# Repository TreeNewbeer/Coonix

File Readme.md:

# Coonix

_Coonix_ is a funny project about building a application platform in Allwinner-v3s processor or nuvoton nuc980 processor.

### The structure of _Coonix_ is shown as follow:

## How to use
* TODO

## TODO
* Hardware schematic diagram
* Linux porting

## License

* MIT License

## Contributing

If you are pleased with this project, give me _Star_ rather than coffee:)

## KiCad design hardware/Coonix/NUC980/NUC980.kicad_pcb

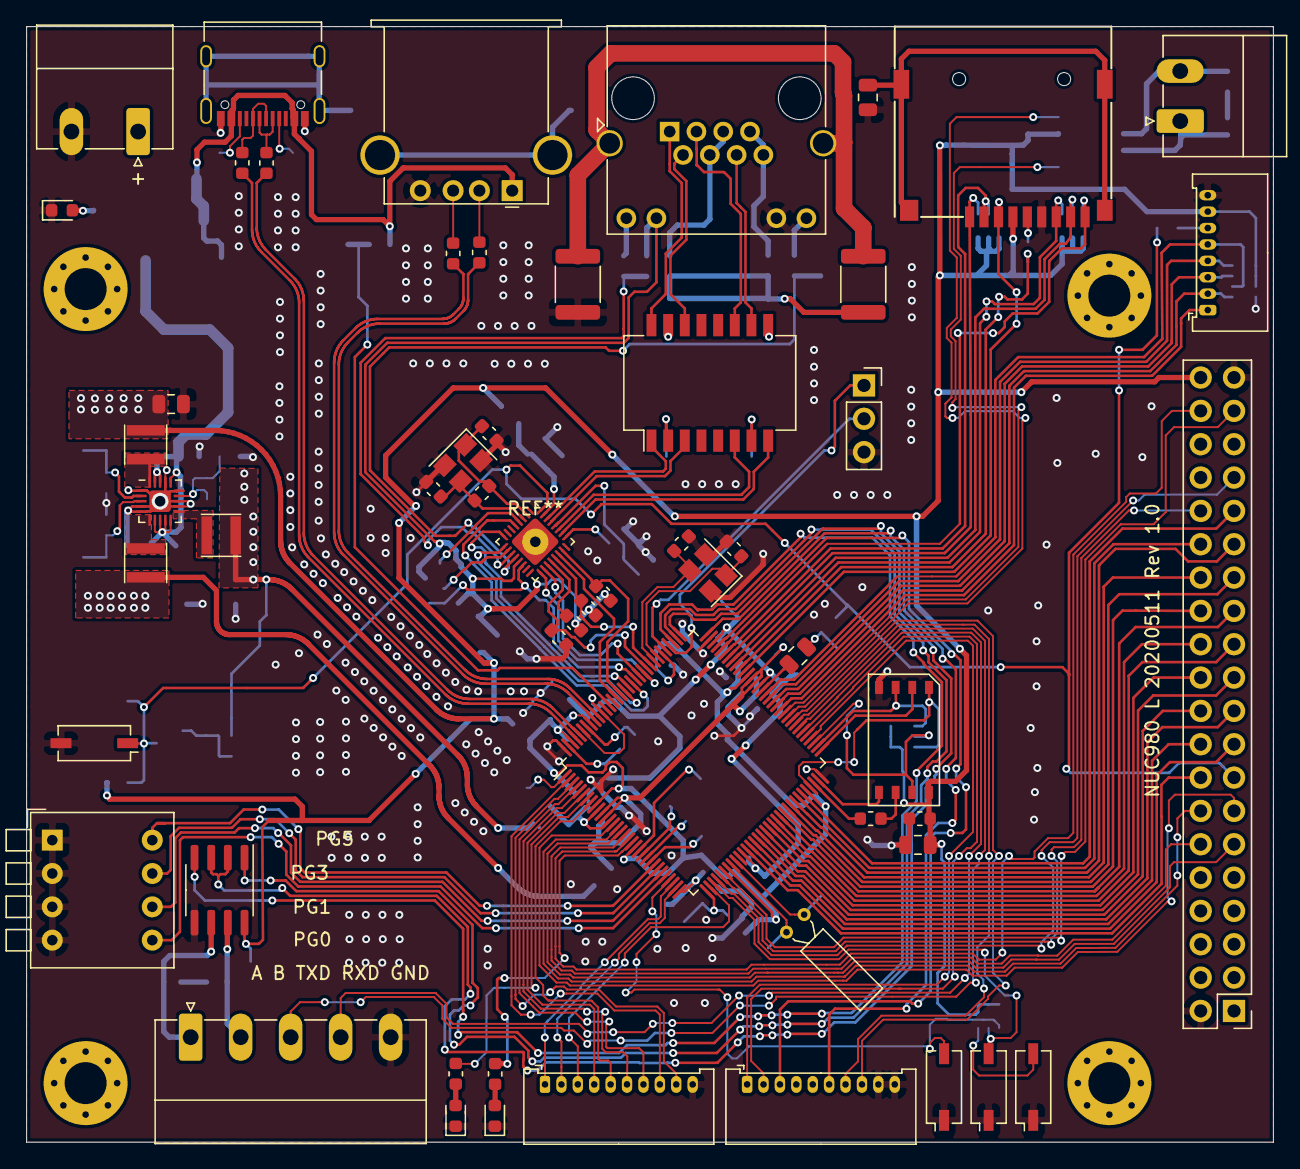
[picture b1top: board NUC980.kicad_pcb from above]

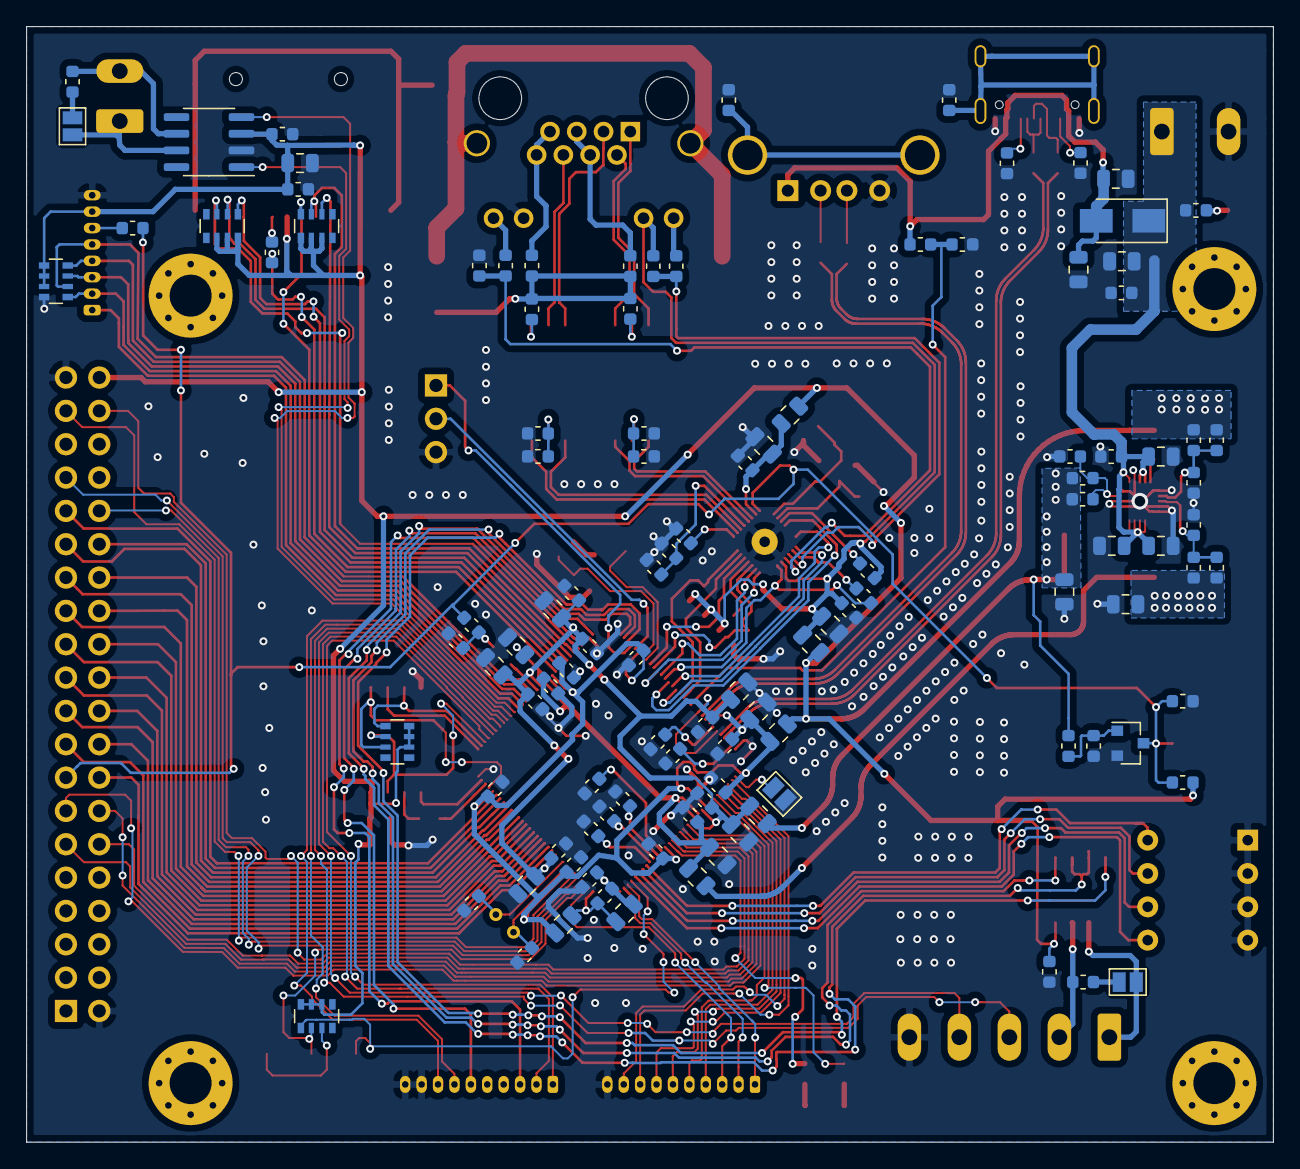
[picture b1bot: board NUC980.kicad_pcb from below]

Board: 2 copper layers, 95.0 x 85.0 mm, 171 parts (112 on the bottom side), 172 nets.

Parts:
C201, C202: 0.01uF/2KV; C_1812_4532Metric
C203, C205, C207, C303, C304: 0.01uF; C_0603_1608Metric
C204, C206, C208, C212, C213, C305, C402, C501, C711, C713, C714, C715, C716, C717, C718, C720, C722, C724, C726, C728, C729, C731, C735, C737, C1001, C1101: 0.1uF; C_0603_1608Metric
C209, C214: 30pF; C_0603_1608Metric
C210, C211, C301, C302, C306, C401, C502, C707, C708, C710, C719, C721, C723, C725, C727, C730, C736, C738, C739, C740, C741, C742: 10uF; C_0805_2012Metric
C701, C702, C704, C705: 15pF; C_0603_1608Metric
C703: 1nF; C_0603_1608Metric
C706, C709, C712: 1uF; C_0603_1608Metric
C732, C733, C734: 18pF; C_0603_1608Metric
D301, D1202: GREEN; LED_0603_1608Metric
D302: SS14; D_SMA
D1201: RED; LED_0603_1608Metric
FB201, FB202, FB501, FB701, FB702, FB703, FB704, FB705: 120R; L_0805_2012Metric
H301, H302, H303, H304: MountingHole; MountingHole_3.2mm_M3_Pad_Via
J201: 8P8C_LED_Shielded; RJ45_Amphenol_RJHSE538X
J301: USB_A; USB_A_Stewart_SS-52100-001_Horizontal
J302: USB_C_Receptacle; USB_C_Receptacle_Palconn_UTC16-G
J303: POWER; PhoenixContact_MC_1,5_2-G-5.08_1x02_P5.08mm_Horizontal
J501: Micro_SD_Card; MicroSD
J601, J901: Conn_01x10; Molex_PicoBlade_53048-1010_1x10_P1.25mm_Horizontal
J701: Debug_UART; PinSocket_1x03_P2.54mm_Vertical
J702: JTAG; Molex_PicoBlade_53048-0810_1x08_P1.25mm_Horizontal
J801: AC1583; PinHeader_2x20_P2.54mm_Vertical
J1001: Conn_01x05; PhoenixContact_MC_1,5_5-G-3.81_1x05_P3.81mm_Horizontal
J1101: Conn_01x02; PhoenixContact_MC_1,5_2-G-3.81_1x02_P3.81mm_Horizontal
JP301: USB0 Host/Device; SolderJumper-2_P1.3mm_Open_Pad1.0x1.5mm
JP1001, JP1101: JP; SolderJumper-2_P1.3mm_Open_Pad1.0x1.5mm
L701, L702, L703: 2.2uH 1.5A; L_Taiyo-Yuden_NR-30xx
Q701: MMBT3904; SOT-23
R201, R204: 330R; R_0603_1608Metric
R202, R203, R212, R213, R214, R305, R306: 5.1K; R_0603_1608Metric
R205, R211, R307: 10K; R_0603_1608Metric
R206, R401, R501, R704, R713: 0R; R_0603_1608Metric
R207, R208, R209, R210: 75R; R_0603_1608Metric
R215: 6.19K; R_0603_1608Metric
R216: 1M; R_0603_1608Metric
R301, R302, R303, R304: 22R; R_0603_1608Metric
R308: 20K; R_0603_1608Metric
R309: 39K; R_0603_1608Metric
R701: 470R; R_0603_1608Metric
R702, R703: 12.1K; R_0603_1608Metric
R705, R706, R707, R708, R710: 100K; R_0603_1608Metric
R709: 200K; R_0603_1608Metric
R711: 68K; R_0603_1608Metric
R712: 15K; R_0603_1608Metric
R718, R719, R720, R721: NC; R_0603_1608Metric
R1001, R1101: 120R; R_0603_1608Metric
R1201, R1202: 4.7K; R_0603_1608Metric
RN401, RN501, RN502, RN701, RN1201: 10Kx4; R_Array_Convex_4x0603
SW701: RESET; SW_DIP_SPSTx01_Slide_Copal_CHS-01A_W5.08mm_P1.27mm_JPin
SW702: SW_DIP_x04; SW_DIP_SPSTx04_Piano_10.8x11.72mm_W7.62mm_P2.54mm
SW1201, SW1202, SW1203: SW_Push; SW_DIP_SPSTx01_Slide_Copal_CHS-01A_W5.08mm_P1.27mm_JPin
TR201: PT61017PEL; Transformer_Ethernet_Bourns_PT61017PEL
U201: NUC980DK; LQFP-128_14x14mm_P0.4mm
U202: IP101GR; QFN-32-1EP_4x4mm_P0.4mm_EP2.65x2.65mm
U401: W25N01GV; Mi
U701: EA3036; QFN-20-1EP_3x3mm_P0.4mm_EP1.65x1.65mm
U1001: MAX485E; SOIC-8_3.9x4.9mm_P1.27mm
U1101: SN65HVD232; SOIC-8_3.9x4.9mm_P1.27mm
Y201: 25MHz; Crystal_SMD_3225-4Pin_3.2x2.5mm
Y701: 32.768KHz; Crystal_DS26_D2.0mm_L6.0mm_Horizontal
Y702: 12MHz; Crystal_SMD_3225-4Pin_3.2x2.5mm

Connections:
+1V2: C706.1, C732.1, C740.1, FB702.2, L701.2, R707.1
+1V8: C733.1, C741.1, FB704.2, L702.2, R709.1
+3V3: C401.2, C402.2, C501.1, C502.1, C734.1, C742.1, C1001.2, C1101.2, FB201.2, FB202.2, FB703.2, J501.4, J702.7, J801.40, L703.2, R706.2, R711.1, RN401.6, RN401.7, RN401.8, RN501.5, RN501.6, RN501.7, RN502.6, RN502.7, RN502.8, RN701.5, RN701.6, RN701.7, RN1201.6, RN1201.7, RN1201.8, U401.8, U1001.8, U1101.3
+5V: C305.1, C306.1, C707.1, C708.1, C710.1, C712.1, D302.1, J303.1, R307.1, U701.7, U701.8, U701.9, U701.10, U701.16, U701.18, U701.19
/CAN1_RXD: U201.74, U1101.4
/CAN1_TXD: U201.75, U1101.1
/DO0: J901.6, U201.96
/DO1: J901.2, U201.69
/DO2: J901.1, U201.68
/ETH/ETH_COL: R205.2, U202.4
/ETH/ETH_CRS: R211.1, U202.20
/ETH/ETH_PHY_AD0: R203.2, R204.2, U202.11
/ETH/ETH_PHY_AD3: R201.2, R202.2, U202.12
/ETH/ETH_RX_CLK: R206.2, U202.10
/ETH/ETH_RX_N: J201.6, TR201.10
/ETH/ETH_RX_P: J201.3, TR201.11
/ETH/ETH_TX_N: J201.2, TR201.14
/ETH/ETH_TX_P: J201.1, TR201.16
/ETH/ETH_XI: C209.1, R216.2, U202.2, Y201.1
/ETH/ETH_XO: C214.1, R216.1, U202.3, Y201.3
/ETH/MDI_RX_N: TR201.8, U202.26
/ETH/MDI_RX_P: TR201.6, U202.27
/ETH/MDI_TX_N: TR201.3, U202.29
/ETH/MDI_TX_P: TR201.1, U202.30
/ETH/PHY_AVDD: C210.1, C212.1, FB201.1, U202.31
/ETH/PHY_DVDD: C211.1, C213.1, FB202.1, J201.10, R203.1, R205.1, R211.2, R212.2, R213.2, U202.13
/ETH/RJ45_SH: C201.2, C202.2, J201.SH
/I2C0_SCL: J601.9, U201.3
/I2C0_SDA: J601.8, U201.2
/I2S0_BCLK: J601.6, U201.5
/I2S0_LRCK: J601.7, U201.4
/I2S0_MCLK: J601.5, U201.8
/I2S0_SD: J601.4, U201.6
/LCD_BL: J801.38, U201.18
/LCD_CS: J801.11, U201.16
/LCD_D0: J801.16, U201.44
/LCD_D1: J801.17, U201.45
/LCD_D2: J801.18, U201.46
/LCD_D3: J801.19, U201.47
/LCD_D4: J801.20, U201.48
/LCD_D5: J801.21, U201.49
/LCD_D6: J801.22, U201.50
/LCD_D7: J801.23, U201.51
/LCD_D8: J801.24, U201.52
/LCD_D9: J801.25, U201.53
/LCD_D10: J801.26, U201.54
/LCD_D11: J801.27, U201.55
/LCD_D12: J801.28, U201.56
/LCD_D13: J801.29, U201.57
/LCD_D14: J801.30, U201.58
/LCD_D15: J801.31, U201.59
/LCD_RD: J801.14, U201.15
/LCD_RS: J801.12, U201.17
/LCD_WR: J801.13, U201.14
/LED/LED_G: R1202.1, U201.19
/LED/LED_R: R1201.1, U201.7
/LED/SW_K3: RN1201.3, SW1203.2
/NUC980_CORE/12M_IN: C705.1, U201.103, Y702.1
/NUC980_CORE/12M_OUT: C704.1, U201.104, Y702.3
/NUC980_CORE/32K_IN: C701.1, U201.40, Y701.1
/NUC980_CORE/32K_OUT: C702.1, U201.41, Y701.2
/NUC980_CORE/AVDD33: C737.1, C739.1, FB705.1, U201.33
/NUC980_CORE/AVSS: C737.2, C739.2, R713.1, U201.32
/NUC980_CORE/PB0: RN1201.1, SW1201.2, U201.29
/NUC980_CORE/PB5: RN1201.2, SW1202.2, U201.35
/NUC980_CORE/TCK: J702.2, RN701.1, U201.77
/NUC980_CORE/TDI: J702.4, RN701.4, U201.79
/NUC980_CORE/TDO: J702.1, U201.76
/NUC980_CORE/TMS: J702.3, RN701.3, U201.78
/NUC980_CORE/TRST: J702.5, RN701.2, U201.80
/NUC980_CORE/U0RXD: J701.1, U201.100
/NUC980_CORE/U0TXD: J701.2, U201.101
/NUC980_CORE/VDD12: C711.1, C713.1, C714.1, C715.1, C716.1, C717.1, C719.1, C721.1, C723.1, C725.1, C727.1, FB702.1, U201.10, U201.13, U201.43, U201.82, U201.94, U201.118, U201.123
/NUC980_CORE/VDD18: C731.1, C735.1, C736.1, C738.1, FB704.1, U201.11, U201.12, U201.83, U201.84
/NUC980_CORE/VDD33: C718.1, C720.1, C722.1, C724.1, C726.1, C728.1, C729.1, C730.1, FB703.1, FB705.2, U201.9, U201.20, U201.39, U201.60, U201.85, U201.102, U201.121, U201.126
/PE0: R213.1, U201.105, U202.21
/PE1: R214.1, U201.106, U202.19
/PE2: U201.107, U202.17
/PE3: U201.108, U202.18
/PE4: R206.1, U201.109, U202.14
/PE5: U201.110, U202.5
/PE6: U201.111, U202.8
/PE7: U201.112, U202.9
/PE8: R212.1, U201.113, U202.23
/PE9: U201.114, U202.22
/PE11: R308.2, R309.1, U201.116
/PWM00: J901.7, U201.72
/PWM01: J901.8, U201.73
/PWM02: J901.3, U201.93
/QSPI/CLK: R401.2, U401.6
/QSPI_CLK: R401.1, U201.62
/QSPI_CS: RN401.3, U201.61, U401.1
/QSPI_IO0: U201.63, U401.5
/QSPI_IO1: U201.65, U401.2
/QSPI_IO2: RN401.1, U201.66, U401.3
/QSPI_IO3: RN401.2, U201.67, U401.7
/SD0_CD: J501.9, RN502.3, U201.92
/SD0_CLK: R501.2, U201.87
/SD0_CMD: J501.3, RN501.4, U201.86
/SD0_D0: J501.7, RN502.1, U201.88
/SD0_D1: J501.8, RN502.2, U201.89
/SD0_D2: J501.1, RN501.2, U201.90
/SD0_D3: J501.2, RN501.3, U201.91
/SPI1_CLK: J601.2, U201.31
/SPI1_CS: J601.1, U201.30
/SPI1_MOSI: J601.3, U201.34
/TOUCH_INT: J801.37, U201.38
/TOUCH_SCL: J801.32, U201.37
/TOUCH_SDA: J801.33, U201.36
/U1RTS: U201.97, U1001.2, U1001.3
/U1RXD: U201.98, U1001.1
/U1TXD: U201.99, U1001.4
/U6RXD: J1001.3, U201.71
/U6TXD: J1001.4, U201.70
/UART/RS485_A: J1001.1, JP1001.2, U1001.6
/UART/RS485_B: J1001.2, R1001.2, U1001.7
/USB0_D+: R302.2, U201.125
/USB0_D-: R301.2, U201.124
/USB0_ID: JP301.1, U201.1
/USB1_D+: R303.2, U201.120
/USB1_D-: R304.2, U201.119
/~RST: C709.1, J801.15, Q701.3, R701.1, R704.2, R706.1, SW701.1, U202.32
GNDD: C202.1, C203.2, C204.2, C205.2, C206.2, C207.2, C208.2, C209.2, C210.2, C211.2, C212.2, C213.2, C214.2, C301.2, C302.2, C303.2, C304.1, C305.2, C306.2, C401.1, C402.1, C501.2, C502.2, C701.2, C702.2, C703.1, C704.2, C705.2, C707.2, C708.2, C709.2, C710.2, C711.2, C712.2, C713.2, C714.2, C715.2, C716.2, C717.2, C718.2, C719.2, C720.2, C721.2, C722.2, C723.2, C724.2, C725.2, C726.2, C727.2, C728.2, C729.2, C730.2, C731.2, C735.2, C736.2, C738.2, C740.2, C741.2, C742.2, C1001.1, C1101.1, D301.1, D1201.1, D1202.1, FB501.2, J201.11, J301.4, J302.A1, J302.A12, J302.B1, J302.B12, J303.2, J501.6, J601.10, J701.3, J702.8, J801.2, J801.39, J901.9, J901.10, J1001.5, JP301.2, Q701.2, R202.1, R214.2, R215.1, R305.2, R306.2, R309.2, R702.1, R703.1, R705.1, R708.1, R710.1, R712.1, R713.2, R718.1, R719.1, R720.1, R721.1, RN701.8, SW701.2, SW702.1, SW702.2, SW702.3, SW702.4, SW1201.1, SW1202.1, SW1203.1, U201.64, U201.95, U201.128, U401.4, U701.1, U701.4, U701.5, U701.12, U701.13, U701.15, U701.17, U701.21, U1001.5, U1101.2, Y201.2, Y201.4, Y702.2, Y702.4
unnamed: C201.1, R207.2, R208.2, R209.2, R210.2
unnamed: C203.1, C204.1, TR201.7
unnamed: C205.1, C206.1, TR201.2
unnamed: C207.1, C208.1, U202.28
unnamed: C303.1, J301.5
unnamed: C304.2, J302.S1
unnamed: C703.2, FB701.2, R701.2
unnamed: C706.2, Q701.1, R705.2
unnamed: C732.2, R707.2, R708.2, U701.14
unnamed: C733.2, R709.2, R710.2, U701.3
unnamed: C734.2, R711.2, R712.2, U701.2
unnamed: D301.2, R307.2
unnamed: D1201.2, R1201.2
unnamed: D1202.2, R1202.2
unnamed: FB501.1, J501.10
unnamed: FB701.1, U201.81
unnamed: J201.4, J201.5, R208.1
unnamed: J201.7, J201.8, R207.1
unnamed: J201.9, R204.1
unnamed: J201.12, R201.1
unnamed: J301.2, R304.1
unnamed: J301.3, R303.1
unnamed: J302.A5, R305.1
unnamed: J302.A6, J302.B6, R302.1
unnamed: J302.A7, J302.B7, R301.1
unnamed: J302.B5, R306.1
unnamed: J501.5, R501.1
unnamed: J702.6, R704.1
unnamed: J1101.1, JP1101.2, U1101.7
unnamed: J1101.2, R1101.2, U1101.6
unnamed: JP1001.1, R1001.1
unnamed: JP1101.1, R1101.1
unnamed: L701.1, U701.11
unnamed: L702.1, U701.6
unnamed: L703.1, U701.20
unnamed: R209.1, TR201.15
unnamed: R210.1, TR201.9
unnamed: R215.2, U202.25
unnamed: R702.2, U201.122
unnamed: R703.2, U201.127
unnamed: R718.2, U201.24
unnamed: R719.2, U201.23
unnamed: R720.2, U201.22
unnamed: R721.2, U201.21
unnamed: SW702.5, U201.28
unnamed: SW702.6, U201.27
unnamed: SW702.7, U201.26
unnamed: SW702.8, U201.25
VBUS: C301.1, C302.1, D302.2, J301.1, J302.A4, J302.A9, J302.B4, J302.B9, R308.1

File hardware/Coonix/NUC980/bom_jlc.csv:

Comment,Description,Designator,Footprint,LibRef,Pins,Quantity
IP101GR,U202,U202,Package_DFN_QFN:QFN-32-1EP_4x4mm_P0.4mm_EP2.65x2.65mm,,2,1
8P8C_LED_Shielded,J201,J201,Connector_RJ:RJ45_Amphenol_RJHSE538X,,2,1
5.1K,R202,R202,0603,,2,1
330R,R201,R201,0603,,2,1
5.1K,R203,R203,0603,,2,1
330R,R204,R204,0603,,2,1
PT61017PEL,TR201,TR201,Transformer_SMD:Transformer_Ethernet_Bourns_PT61017PEL,,2,1
75R,R207,R207,0603,,2,1
75R,R208,R208,0603,,2,1
75R,R210,R210,0603,,2,1
75R,R209,R209,0603,,2,1
0.01uF/2KV,C201,C201,Capacitor_SMD:C_1812_4532Metric,,2,1
0.01uF,C203,C203,0603,,2,1
0.1uF,C204,C204,0603,,2,1
0.01uF,C205,C205,0603,,2,1
0.1uF,C206,C206,0603,,2,1
0.01uF/2KV,C202,C202,Capacitor_SMD:C_1812_4532Metric,,2,1
120R,FB202,FB202,0805,,2,1
0.1uF,C213,C213,0603,,2,1
10uF,C211,C211,0805,,2,1
120R,FB201,FB201,0805,,2,1
0.1uF,C212,C212,0603,,2,1
10uF,C210,C210,0805,,2,1
25MHz,Y201,Y201,Crystal:Crystal_SMD_3225-4Pin_3.2x2.5mm,,2,1
1M,R216,R216,0603,,2,1
30pF,C209,C209,0603,,2,1
30pF,C214,C214,0603,,2,1
0R,R206,R206,0603,,2,1
0.01uF,C207,C207,0603,,2,1
0.1uF,C208,C208,0603,,2,1
6.19K,R215,R215,0603,,2,1
5.1K,R212,R212,0603,,2,1
5.1K,R213,R213,0603,,2,1
5.1K,R214,R214,0603,,2,1
10K,R211,R211,0603,,2,1
10K,R205,R205,0603,,2,1
USB_A,J301,J301,Connector_USB:USB_A_Stewart_SS-52100-001_Horizontal,,2,1
USB_C_Receptacle,J302,J302,Connector_USB:USB_C_Receptacle_Palconn_UTC16-G,,2,1
0.01uF,C303,C303,0603,,2,1
22R,R303,R303,0603,,2,1
22R,R304,R304,0603,,2,1
0.01uF,C304,C304,0603,,2,1
22R,R301,R301,0603,,2,1
22R,R302,R302,0603,,2,1
5.1K,R305,R305,0603,,2,1
5.1K,R306,R306,0603,,2,1
USB0 Host/Device,JP301,JP301,Jumper:SolderJumper-2_P1.3mm_Open_Pad1.0x1.5mm,,2,1
10uF,C301,C301,0805,,2,1
10uF,C302,C302,0805,,2,1
20K,R308,R308,0603,,2,1
39K,R309,R309,0603,,2,1
POWER,J303,J303,"Connector_Phoenix_MC_HighVoltage:PhoenixContact_MC_1,5_2-G-5.08_1x02_P5.08mm_Horizontal",,2,1
SS14,D302,D302,Diode_SMD:D_SMA,,2,1
10uF,C306,C306,0805,,2,1
0.1uF,C305,C305,0603,,2,1
10K,R307,R307,0603,,2,1
GREEN,D301,D301,LED_SMD:LED_0603_1608Metric,,2,1
MountingHole,H301,H301,MountingHole:MountingHole_3.2mm_M3_Pad_Via,,2,1
MountingHole,H302,H302,MountingHole:MountingHole_3.2mm_M3_Pad_Via,,2,1
MountingHole,H303,H303,MountingHole:MountingHole_3.2mm_M3_Pad_Via,,2,1
MountingHole,H304,H304,MountingHole:MountingHole_3.2mm_M3_Pad_Via,,2,1
W25N01GV,U401,U401,MicroSD:Mi,,2,1
10uF,C401,C401,0805,,2,1
0.1uF,C402,C402,0603,,2,1
0R,R401,R401,0603,,2,1
10Kx4,RN401,RN401,Resistor_SMD:R_Array_Convex_4x0603,,2,1
0R,R501,R501,0603,,2,1
120R,FB501,FB501,0805,,2,1
0.1uF,C501,C501,0603,,2,1
10uF,C502,C502,0805,,2,1
Micro_SD_Card,J501,J501,MicroSD:MicroSD,,2,1
10Kx4,RN501,RN501,Resistor_SMD:R_Array_Convex_4x0603,,2,1
10Kx4,RN502,RN502,Resistor_SMD:R_Array_Convex_4x0603,,2,1
Conn_01x10,J601,J601,Connector_Molex:Molex_PicoBlade_53048-1010_1x10_P1.25mm_Horizontal,,2,1
NUC980DK,U201,U201,Package_QFP:LQFP-128_14x14mm_P0.4mm,,2,1
JTAG,J702,J702,Connector_Molex:Molex_PicoBlade_53048-0810_1x08_P1.25mm_Horizontal,,2,1
0R,R704,R704,0603,,2,1
10Kx4,RN701,RN701,Resistor_SMD:R_Array_Convex_4x0603,,2,1
EA3036,U701,U701,Package_DFN_QFN:QFN-20-1EP_3x3mm_P0.4mm_EP1.65x1.65mm,,2,1
2.2uH 1.5A,L701,L701,Inductor_SMD:L_Taiyo-Yuden_NR-30xx,,2,1
100K,R707,R707,0603,,2,1
10uF,C740,C740,0805,,2,1
100K,R708,R708,0603,,2,1
18pF,C732,C732,0603,,2,1
2.2uH 1.5A,L702,L702,Inductor_SMD:L_Taiyo-Yuden_NR-30xx,,2,1
200K,R709,R709,0603,,2,1
10uF,C741,C741,0805,,2,1
100K,R710,R710,0603,,2,1
18pF,C733,C733,0603,,2,1
2.2uH 1.5A,L703,L703,Inductor_SMD:L_Taiyo-Yuden_NR-30xx,,2,1
68K,R711,R711,0603,,2,1
10uF,C742,C742,0805,,2,1
15K,R712,R712,0603,,2,1
18pF,C734,C734,0603,,2,1
10uF,C707,C707,0805,,2,1
10uF,C708,C708,0805,,2,1
10uF,C710,C710,0805,,2,1
1uF,C712,C712,0603,,2,1
0.1uF,C718,C718,0603,,2,1
0.1uF,C720,C720,0603,,2,1
0.1uF,C722,C722,0603,,2,1
0.1uF,C724,C724,0603,,2,1
0.1uF,C726,C726,0603,,2,1
0.1uF,C728,C728,0603,,2,1
0.1uF,C729,C729,0603,,2,1
10uF,C730,C730,0805,,2,1
0.1uF,C737,C737,0603,,2,1
10uF,C739,C739,0805,,2,1
120R,FB705,FB705,0805,,2,1
120R,FB703,FB703,0805,,2,1
0R,R713,R713,0603,,2,1
0.1uF,C711,C711,0603,,2,1
0.1uF,C713,C713,0603,,2,1
0.1uF,C714,C714,0603,,2,1
0.1uF,C715,C715,0603,,2,1
0.1uF,C716,C716,0603,,2,1
0.1uF,C717,C717,0603,,2,1
10uF,C721,C721,0805,,2,1
120R,FB702,FB702,0805,,2,1
10uF,C719,C719,0805,,2,1
10uF,C723,C723,0805,,2,1
10uF,C725,C725,0805,,2,1
10uF,C727,C727,0805,,2,1
120R,FB704,FB704,0805,,2,1
0.1uF,C731,C731,0603,,2,1
0.1uF,C735,C735,0603,,2,1
10uF,C738,C738,0805,,2,1
10uF,C736,C736,0805,,2,1
1uF,C706,C706,0603,,2,1
100K,R705,R705,0603,,2,1
MMBT3904,Q701,Q701,Package_TO_SOT_SMD:SOT-23,,2,1
1uF,C709,C709,0603,,2,1
100K,R706,R706,0603,,2,1
RESET,SW701,SW701,Button_Switch_SMD:SW_DIP_SPSTx01_Slide_Copal_CHS-01A_W5.08mm_P1.27mm_JPin,,2,1
470R,R701,R701,0603,,2,1
1nF,C703,C703,0603,,2,1
120R,FB701,FB701,0805,,2,1
12MHz,Y702,Y702,Crystal:Crystal_SMD_3225-4Pin_3.2x2.5mm,,2,1
15pF,C704,C704,0603,,2,1
15pF,C705,C705,0603,,2,1
32.768KHz,Y701,Y701,Crystal:Crystal_DS26_D2.0mm_L6.0mm_Horizontal,,2,1
15pF,C701,C701,0603,,2,1
15pF,C702,C702,0603,,2,1
12.1K,R703,R703,0603,,2,1
12.1K,R702,R702,0603,,2,1
Debug_UART,J701,J701,Connector_PinSocket_2.54mm:PinSocket_1x03_P2.54mm_Vertical,,2,1
NC,R719,R719,0603,,2,1
NC,R720,R720,0603,,2,1
NC,R721,R721,0603,,2,1
SW_DIP_x04,SW702,SW702,Button_Switch_THT:SW_DIP_SPSTx04_Piano_10.8x11.72mm_W7.62mm_P2.54mm,,2,1
NC,R718,R718,0603,,2,1
AC1583,J801,J801,Connector_PinHeader_2.54mm:PinHeader_2x20_P2.54mm_Vertical,,2,1
Conn_01x10,J901,J901,Connector_Molex:Molex_PicoBlade_53048-1010_1x10_P1.25mm_Horizontal,,2,1
MAX485E,U1001,U1001,Package_SO:SOIC-8_3.9x4.9mm_P1.27mm,,2,1
0.1uF,C1001,C1001,0603,,2,1
Conn_01x05,J1001,J1001,"Connector_Phoenix_MC:PhoenixContact_MC_1,5_5-G-3.81_1x05_P3.81mm_Horizontal",,2,1
120R,R1001,R1001,0603,,2,1
JP,JP1001,JP1001,Jumper:SolderJumper-2_P1.3mm_Open_Pad1.0x1.5mm,,2,1
SN65HVD232,U1101,U1101,Package_SO:SOIC-8_3.9x4.9mm_P1.27mm,,2,1
0.1uF,C1101,C1101,0603,,2,1
Conn_01x02,J1101,J1101,"Connector_Phoenix_MC:PhoenixContact_MC_1,5_2-G-3.81_1x02_P3.81mm_Horizontal",,2,1
120R,R1101,R1101,0603,,2,1
JP,JP1101,JP1101,Jumper:SolderJumper-2_P1.3mm_Open_Pad1.0x1.5mm,,2,1
GREEN,D1202,D1202,LED_SMD:LED_0603_1608Metric,,2,1
RED,D1201,D1201,LED_SMD:LED_0603_1608Metric,,2,1
SW_Push,SW1201,SW1201,Button_Switch_SMD:SW_DIP_SPSTx01_Slide_Copal_CHS-01A_W5.08mm_P1.27mm_JPin,,2,1
SW_Push,SW1202,SW1202,Button_Switch_SMD:SW_DIP_SPSTx01_Slide_Copal_CHS-01A_W5.08mm_P1.27mm_JPin,,2,1
SW_Push,SW1203,SW1203,Button_Switch_SMD:SW_DIP_SPSTx01_Slide_Copal_CHS-01A_W5.08mm_P1.27mm_JPin,,2,1
4.7K,R1201,R1201,0603,,2,1
4.7K,R1202,R1202,0603,,2,1
10Kx4,RN1201,RN1201,Resistor_SMD:R_Array_Convex_4x0603,,2,1

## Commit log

2020-03-31 bugfix:fix readme
2020-04-08 feature(hardware):update V3s and EA3036 schematic symbol (issue:#1,#2)
2020-04-10 feature(hardware):update hardware schematic
2020-04-20 Added something about the nuc980
2020-04-20 add nuc980 sch pcb
2020-05-12 update pcb and add JLC STM pos, bom file
